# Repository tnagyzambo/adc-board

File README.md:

# e003-adc-board

Analog data acquisition board for the ASRP ECU stack. Two general-purpose
channels, sampled simultaneously, configured through an onboard FPGA for load
cells, piezoresistive pressure transducers, 4-20 mA and voltage transmitters,
and referenced to the stack's ground. The thermocouple channels are
`e004-tc-board`. Boards stack to add channels on ASRP-PCB-INTERCONNECT-2,
defined in the design summary, which brings them power from `e001-power-board`
through the ECU MCU board and carries their data to it. The ECU MCU board logs
the data. 60 x 60 mm.

The schematic is drawn; the board has not yet been laid out.

## Documentation

`doc-design/e003-design-summary.typ` records the design intent and, once there
is a board, reviews it against that intent and the device datasheets, with the
schematic as an appendix.

The report builds with [`dcs`](../../../code/dcs). It is built twice:
`e003-design-summary-a4.pdf` to print single sided and keep loose leaf, and
`e003-design-summary-b5.pdf` to print duplex and file in a binder.

```
cd doc-design
dcs build            # or `dcs watch`, or `dcs clean`
dcs open             # editor, build and viewer in one zellij session
```

Everything generated lands in `doc-design/assets/` and is ignored. The footer
stamp names the last commit that touched the report: build after committing and
it names that commit, build mid-edit and it says so.

## Gateware

`gateware/` holds the FPGA's VHDL. The current design is a bring-up image: it
answers on SPI0 with a hello-world string, measures `SYNC_CLK`, switches the
channel supply on command and reads both converters' ID registers. It is
simulated with GHDL and built with Lattice Diamond, both in one Docker
container, and programmed natively from macOS through a J-Link on the
Tag-Connect footprint; `gateware/README.md` gives the full procedure.

## Repository

Part of the ASRP ECU stack. Each board is its own repo, sitting side by
side under `ecad/projects/`: `e001-power-board`, `e002-mcu-board`,
`e003-adc-board`, `e004-tc-board`, `bus-interface`, `ecu-stack` and
`servo-board`. They are separate because they are drawn, revised, fabricated
and released one at a time. Nothing in the KiCad files crosses a board
boundary.

## Branches

- `main` — released revisions and nothing else. One commit per revision,
  squashed from `dev` at release, with the revision in the commit subject:
  `REV A`, `REV B`. `git log --oneline main` is the revision list.
- `dev` — everything in progress.

There are no tags. A revision is a commit on `main`.

This board has no revision yet, so `main` carries only its initial commit, an
empty README. Everything, this README included, lives on `dev`.

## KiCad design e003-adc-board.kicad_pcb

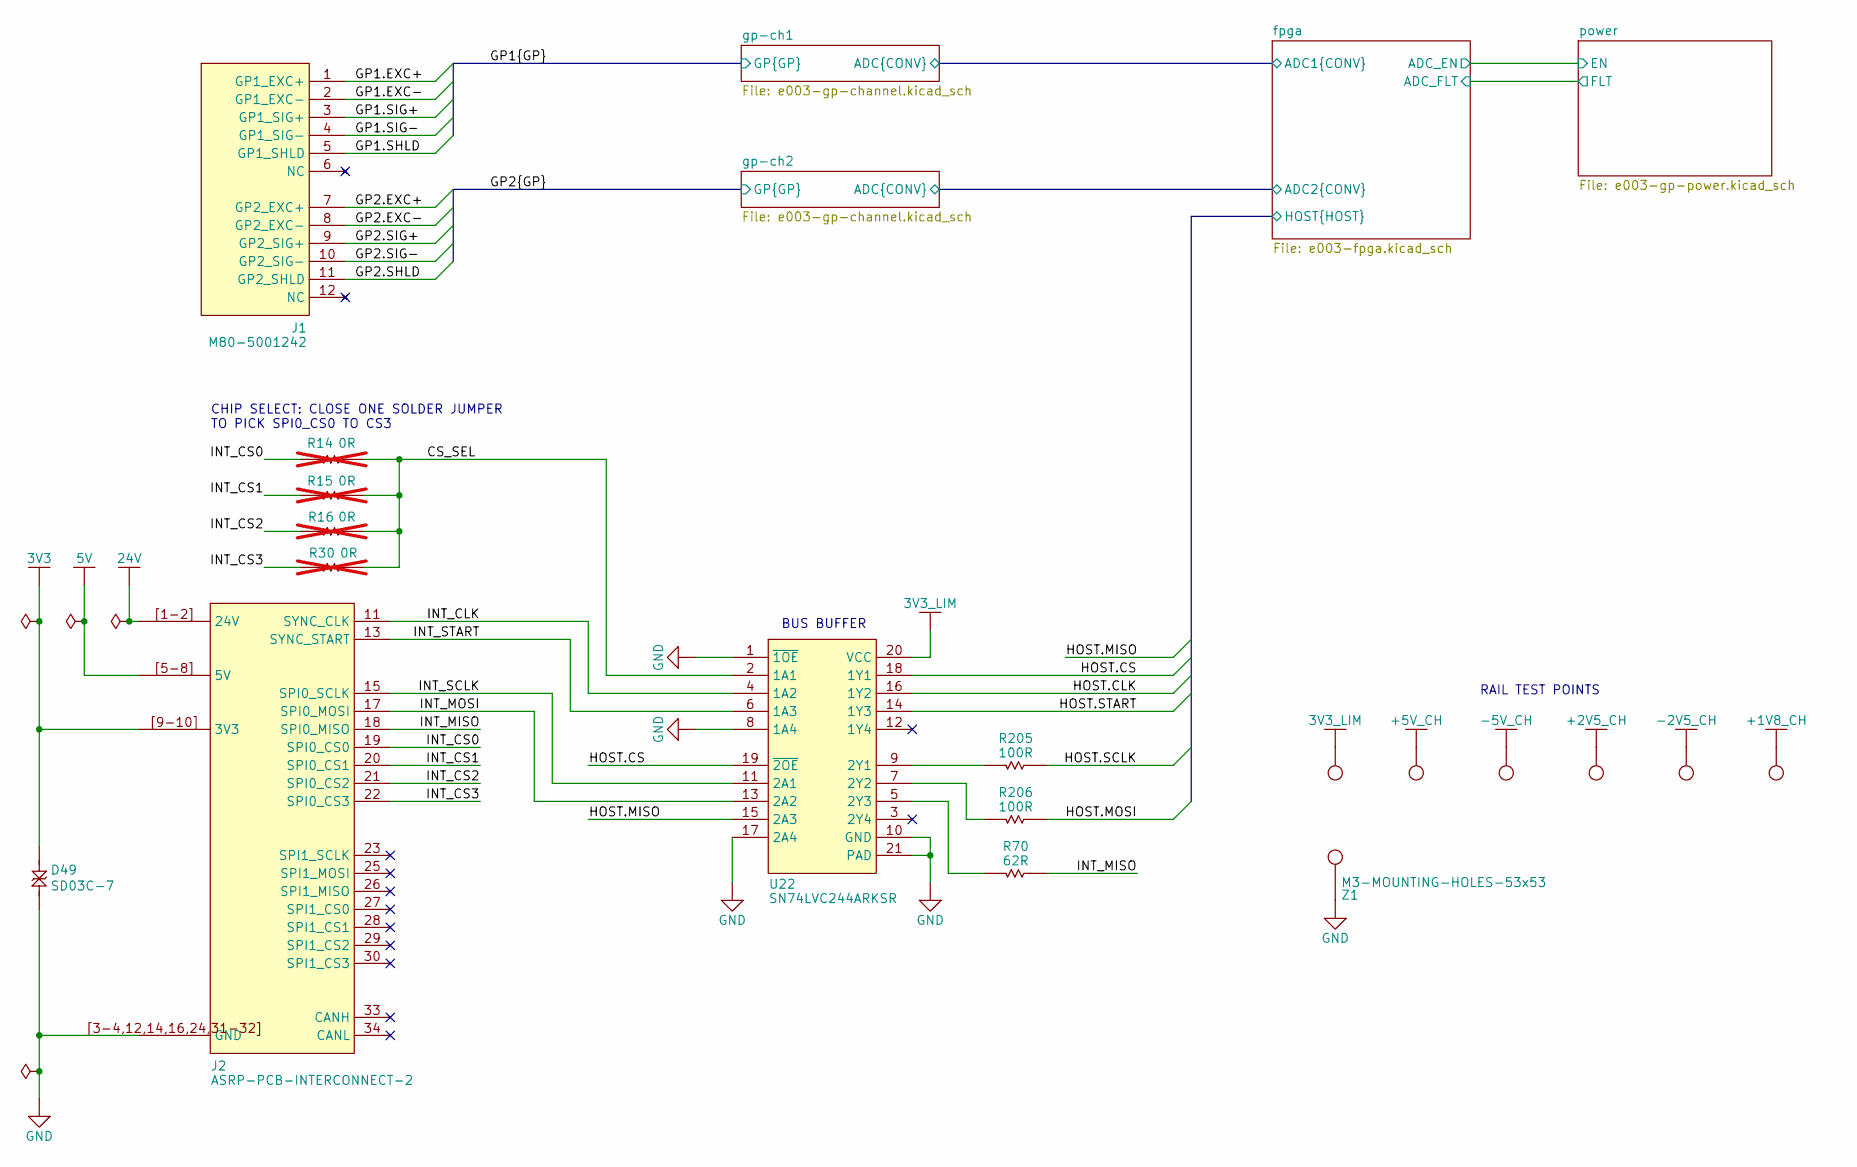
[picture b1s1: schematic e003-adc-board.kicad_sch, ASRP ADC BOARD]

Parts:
D49: SD03C-7; DIODES-SOD323; Voltage_Rating 3.3V; MPN SD03C-7; DigiKey_Part 31-SD03C-7CT-ND
J1: M80-5001242; HARWIN-M80-5001242; MPN M80-5001242; DigiKey_Part 952-1980-ND
J2: ASRP-PCB-INTERCONNECT-2
R14, R15, R16, R30: 0R; VISHAY-0402; Tolerance 1%; MPN CRCW04020000Z0EEHP; DigiKey_Part 541-CRCW04020000Z0EEHPCT-ND; not fitted
R70: 62R; VISHAY-0402; Tolerance 1%; MPN CRCW040262R0FKEDC; DigiKey_Part 541-CRCW040262R0FKEDCCT-ND
R205, R206: 100R; VISHAY-0402; Tolerance 1%; MPN CRCW0402100RFKEDC; DigiKey_Part 541-3962-1-ND
TP2, TP10, TP11, TP12, TP13, TP14: PCB-TEST-POINT; PCB-PROBEPOINT; MPN N/A
U22: SN74LVC244ARKSR; TI-VQFN-RKS0020C; MPN SN74LVC244ARKSR; DigiKey_Part 296-SN74LVC244ARKSRCT-ND
Z1: M3-MOUNTING-HOLES-53x53; PCB-M3-MOUNTING-HOLES-53x53; MPN N/A

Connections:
3V3: D49.1 (A1), J2.[9-10] (3V3); also elsewhere on the board
3V3_LIM: TP2.1 (0_1), U22.20 (VCC); also elsewhere on the board
+1V8_CH: TP14.1 (0_1); also elsewhere on the board
+2V5_CH: TP12.1 (0_1); also elsewhere on the board
+5V_CH: TP10.1 (0_1); also elsewhere on the board
-2V5_CH: TP13.1 (0_1); also elsewhere on the board
-5V_CH: TP11.1 (0_1); also elsewhere on the board
/CS_SEL: R14.1, R15.1, R16.1, R30.1, U22.2 (1A1)
/GP1.EXC+: J1.1 (GP1_EXC+); also elsewhere on the board
/GP1.EXC-: J1.2 (GP1_EXC-); also elsewhere on the board
/GP1.SHLD: J1.5 (GP1_SHLD); also elsewhere on the board
/GP1.SIG+: J1.3 (GP1_SIG+); also elsewhere on the board
/GP1.SIG-: J1.4 (GP1_SIG-); also elsewhere on the board
/GP2.EXC+: J1.7 (GP2_EXC+); also elsewhere on the board
/GP2.EXC-: J1.8 (GP2_EXC-); also elsewhere on the board
/GP2.SHLD: J1.11 (GP2_SHLD); also elsewhere on the board
/GP2.SIG+: J1.9 (GP2_SIG+); also elsewhere on the board
/GP2.SIG-: J1.10 (GP2_SIG-); also elsewhere on the board
/INT_CLK: J2.11 (SYNC_CLK), U22.4 (1A2)
/INT_CS0: J2.19 (SPI0_CS0), R14.2
/INT_CS1: J2.20 (SPI0_CS1), R15.2
/INT_CS2: J2.21 (SPI0_CS2), R16.2
/INT_CS3: J2.22 (SPI0_CS3), R30.2
/INT_MISO: J2.18 (SPI0_MISO), R70.1
/INT_MOSI: J2.17 (SPI0_MOSI), U22.13 (2A2)
/INT_SCLK: J2.15 (SPI0_SCLK), U22.11 (2A1)
/INT_START: J2.13 (SYNC_START), U22.6 (1A3)
/fpga/HOST.CLK: U22.16 (1Y2); also elsewhere on the board
/fpga/HOST.CS: U22.18 (1Y1), U22.19 (~2OE); also elsewhere on the board
/fpga/HOST.MISO: U22.15 (2A3); also elsewhere on the board
/fpga/HOST.MOSI: R206.1; also elsewhere on the board
/fpga/HOST.SCLK: R205.1; also elsewhere on the board
/fpga/HOST.START: U22.14 (1Y3); also elsewhere on the board
GND: D49.2 (A2), J2.[3-4,12,14,16,24,31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 (GND), U22.1 (~1OE), U22.8 (1A4), U22.10 (GND), U22.17 (2A4), U22.21 (PAD), Z1.1; also elsewhere on the board
unnamed: R205.2, U22.9 (2Y1)
unnamed: R206.2, U22.7 (2Y2)
unnamed: R70.2, U22.5 (2Y3)

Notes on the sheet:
CHIP SELECT: CLOSE ONE SOLDER JUMPER TO PICK SPI0_CS0 TO CS3
RAIL TEST POINTS
BUS BUFFER

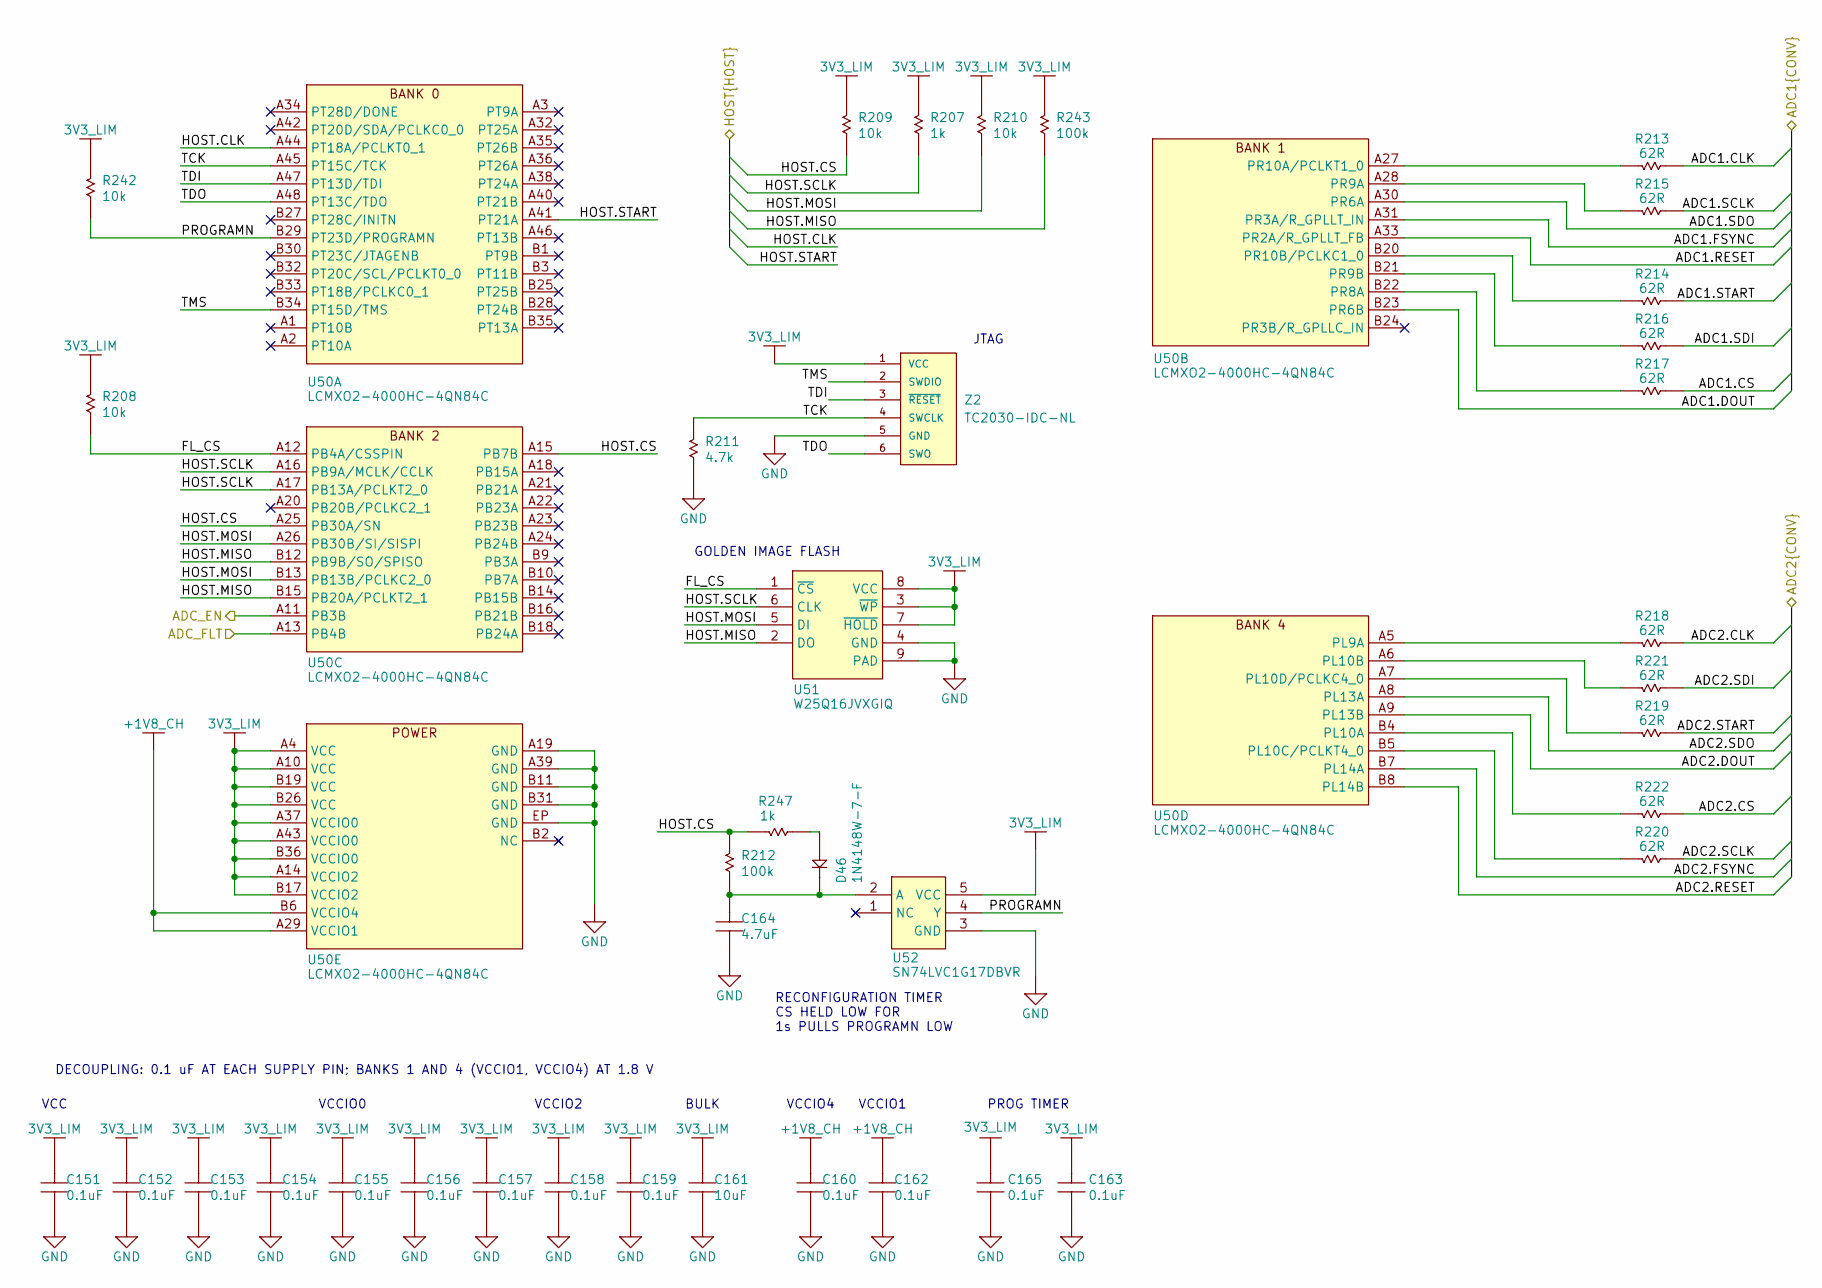
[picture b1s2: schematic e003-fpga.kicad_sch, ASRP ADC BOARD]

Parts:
C151, C152, C153, C154, C155, C156, C157, C158, C159, C160, C162, C163, C165: 0.1uF; MURATA-0402; Tolerance 10%; Voltage_Rating 50 VDC; MPN GRM155R71H104KE14J; DigiKey_Part 490-13342-2-ND
C161: 10uF; MURATA-0805; Tolerance 10%; Voltage_Rating 25 VDC; MPN GRM21BZ71E106KE15K; DigiKey_Part 490-GRM21BZ71E106KE15KCT-ND
C164: 4.7uF; MURATA-0805; Tolerance 10%; Voltage_Rating 25 VDC; MPN GRM21BZ71E475KE15L; DigiKey_Part 490-GRM21BZ71E475KE15LCT-ND
D46: 1N4148W-7-F; DIODES-SOD123; Voltage_Rating 100V; MPN 1N4148W-7-F; DigiKey_Part 1N4148W-FDICT-ND
R207, R247: 1k; VISHAY-0402; Tolerance 1%; MPN CRCW04021K00FKED; DigiKey_Part 541-1.00KLCT-ND
R208, R209, R210, R242: 10k; VISHAY-0402; Tolerance 1%; MPN CRCW040210K0FKEDC; DigiKey_Part 541-3959-1-ND
R211: 4.7k; VISHAY-0402; Tolerance 1%; MPN CRCW04024K70FKED; DigiKey_Part 541-4.70KLCT-ND
R212, R243: 100k; VISHAY-0402; Tolerance 1%; MPN CRCW0402100KFKEDC; DigiKey_Part 541-3960-1-ND
R213, R214, R215, R216, R217, R218, R219, R220, R221, R222: 62R; VISHAY-0402; Tolerance 1%; MPN CRCW040262R0FKEDC; DigiKey_Part 541-CRCW040262R0FKEDCCT-ND
U50: LCMXO2-4000HC-4QN84C; LATTICE-QFN84; MPN LCMXO2-4000HC-4QN84C; DigiKey_Part LCMXO2-4000HC-4QN84C-ND
U51: W25Q16JVXGIQ; WINBOND-XSON8-4X4; MPN W25Q16JVXGIQ; DigiKey_Part none
U52: SN74LVC1G17DBVR; TI-SOT23-DBV0005A; MPN SN74LVC1G17DBVR; DigiKey_Part none
Z2: TC2030-IDC-NL; PCB-TAG-TC2030-IDC-NL; MPN N/A

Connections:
3V3_LIM: C151.2, C152.2, C153.2, C154.2, C155.2, C156.2, C157.2, C158.2, C159.2, C161.2, C163.2, C165.2, R207.2, R208.2, R209.2, R210.2, R242.2, R243.2, U50.A4 (VCC), U50.A10 (VCC), U50.A14 (VCCIO2), U50.A37 (VCCIO0), U50.A43 (VCCIO0), U50.B17 (VCCIO2), U50.B19 (VCC), U50.B26 (VCC), U50.B36 (VCCIO0), U51.3 (~WP), U51.7 (~HOLD), U51.8 (VCC), U52.5 (VCC), Z2.1 (VCC); also elsewhere on the board
+1V8_CH: C160.2, C162.2, U50.A29 (VCCIO1), U50.B6 (VCCIO4); also elsewhere on the board
/fpga/ADC1.CLK: R213.1; also elsewhere on the board
/fpga/ADC1.CS: R217.1; also elsewhere on the board
/fpga/ADC1.DOUT: U50.B23 (PR6B); also elsewhere on the board
/fpga/ADC1.FSYNC: U50.A31 (PR3A/R_GPLLT_IN); also elsewhere on the board
/fpga/ADC1.RESET: U50.A33 (PR2A/R_GPLLT_FB); also elsewhere on the board
/fpga/ADC1.SCLK: R215.1; also elsewhere on the board
/fpga/ADC1.SDI: R216.1; also elsewhere on the board
/fpga/ADC1.SDO: U50.A30 (PR6A); also elsewhere on the board
/fpga/ADC1.START: R214.1; also elsewhere on the board
/fpga/ADC2.CLK: R218.1; also elsewhere on the board
/fpga/ADC2.CS: R222.1; also elsewhere on the board
/fpga/ADC2.DOUT: U50.A9 (PL13B); also elsewhere on the board
/fpga/ADC2.FSYNC: U50.B7 (PL14A); also elsewhere on the board
/fpga/ADC2.RESET: U50.B8 (PL14B); also elsewhere on the board
/fpga/ADC2.SCLK: R220.1; also elsewhere on the board
/fpga/ADC2.SDI: R221.1; also elsewhere on the board
/fpga/ADC2.SDO: U50.A8 (PL13A); also elsewhere on the board
/fpga/ADC2.START: R219.1; also elsewhere on the board
/fpga/ADC_EN: U50.A11 (PB3B); also elsewhere on the board
/fpga/ADC_FLT: U50.A13 (PB4B); also elsewhere on the board
/fpga/FL_CS: R208.1, U50.A12 (PB4A/CSSPIN), U51.1 (~CS)
/fpga/HOST.CLK: U50.A44 (PT18A/PCLKT0_1); also elsewhere on the board
/fpga/HOST.CS: R209.1, R212.2, R247.2, U50.A15 (PB7B), U50.A25 (PB30A/SN); also elsewhere on the board
/fpga/HOST.MISO: R243.1, U50.B12 (PB9B/SO/SPISO), U50.B15 (PB20A/PCLKT2_1), U51.2 (DO); also elsewhere on the board
/fpga/HOST.MOSI: R210.1, U50.A26 (PB30B/SI/SISPI), U50.B13 (PB13B/PCLKC2_0), U51.5 (DI); also elsewhere on the board
/fpga/HOST.SCLK: R207.1, U50.A16 (PB9A/MCLK/CCLK), U50.A17 (PB13A/PCLKT2_0), U51.6 (CLK); also elsewhere on the board
/fpga/HOST.START: U50.A41 (PT21A); also elsewhere on the board
/fpga/PROGRAMN: R242.1, U50.B29 (PT23D/PROGRAMN), U52.4 (Y)
/fpga/TCK: R211.2, U50.A45 (PT15C/TCK), Z2.4 (SWCLK)
/fpga/TDI: U50.A47 (PT13D/TDI), Z2.3 (~RESET)
/fpga/TDO: U50.A48 (PT13C/TDO), Z2.6 (SWO)
/fpga/TMS: U50.B34 (PT15D/TMS), Z2.2 (SWDIO)
GND: C151.1, C152.1, C153.1, C154.1, C155.1, C156.1, C157.1, C158.1, C159.1, C160.1, C161.1, C162.1, C163.1, C164.1, C165.1, R211.1, U50.A19 (GND), U50.A39 (GND), U50.B11 (GND), U50.B31 (GND), U50.EP (GND), U51.4 (GND), U51.9 (PAD), U52.3 (GND), Z2.5 (GND); also elsewhere on the board
unnamed: D46.1 (0), R247.1
unnamed: C164.2, D46.2 (1), R212.1, U52.2 (A)
unnamed: R217.2, U50.B22 (PR8A)
unnamed: R215.2, U50.A28 (PR9A)
unnamed: R216.2, U50.B21 (PR9B)
unnamed: R213.2, U50.A27 (PR10A/PCLKT1_0)
unnamed: R214.2, U50.B20 (PR10B/PCLKC1_0)
unnamed: R218.2, U50.A5 (PL9A)
unnamed: R222.2, U50.B4 (PL10A)
unnamed: R221.2, U50.A6 (PL10B)
unnamed: R220.2, U50.B5 (PL10C/PCLKT4_0)
unnamed: R219.2, U50.A7 (PL10D/PCLKC4_0)

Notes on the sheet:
VCCIO4
VCCIO2
PROG TIMER
GOLDEN IMAGE FLASH
VCC
VCCIO1
RECONFIGURATION TIMER CS HELD LOW FOR 1s PULLS PROGRAMN LOW
JTAG
BULK
DECOUPLING: 0.1 uF AT EACH SUPPLY PIN; BANKS 1 AND 4 (VCCIO1, VCCIO4) AT 1.8 V
VCCIO0

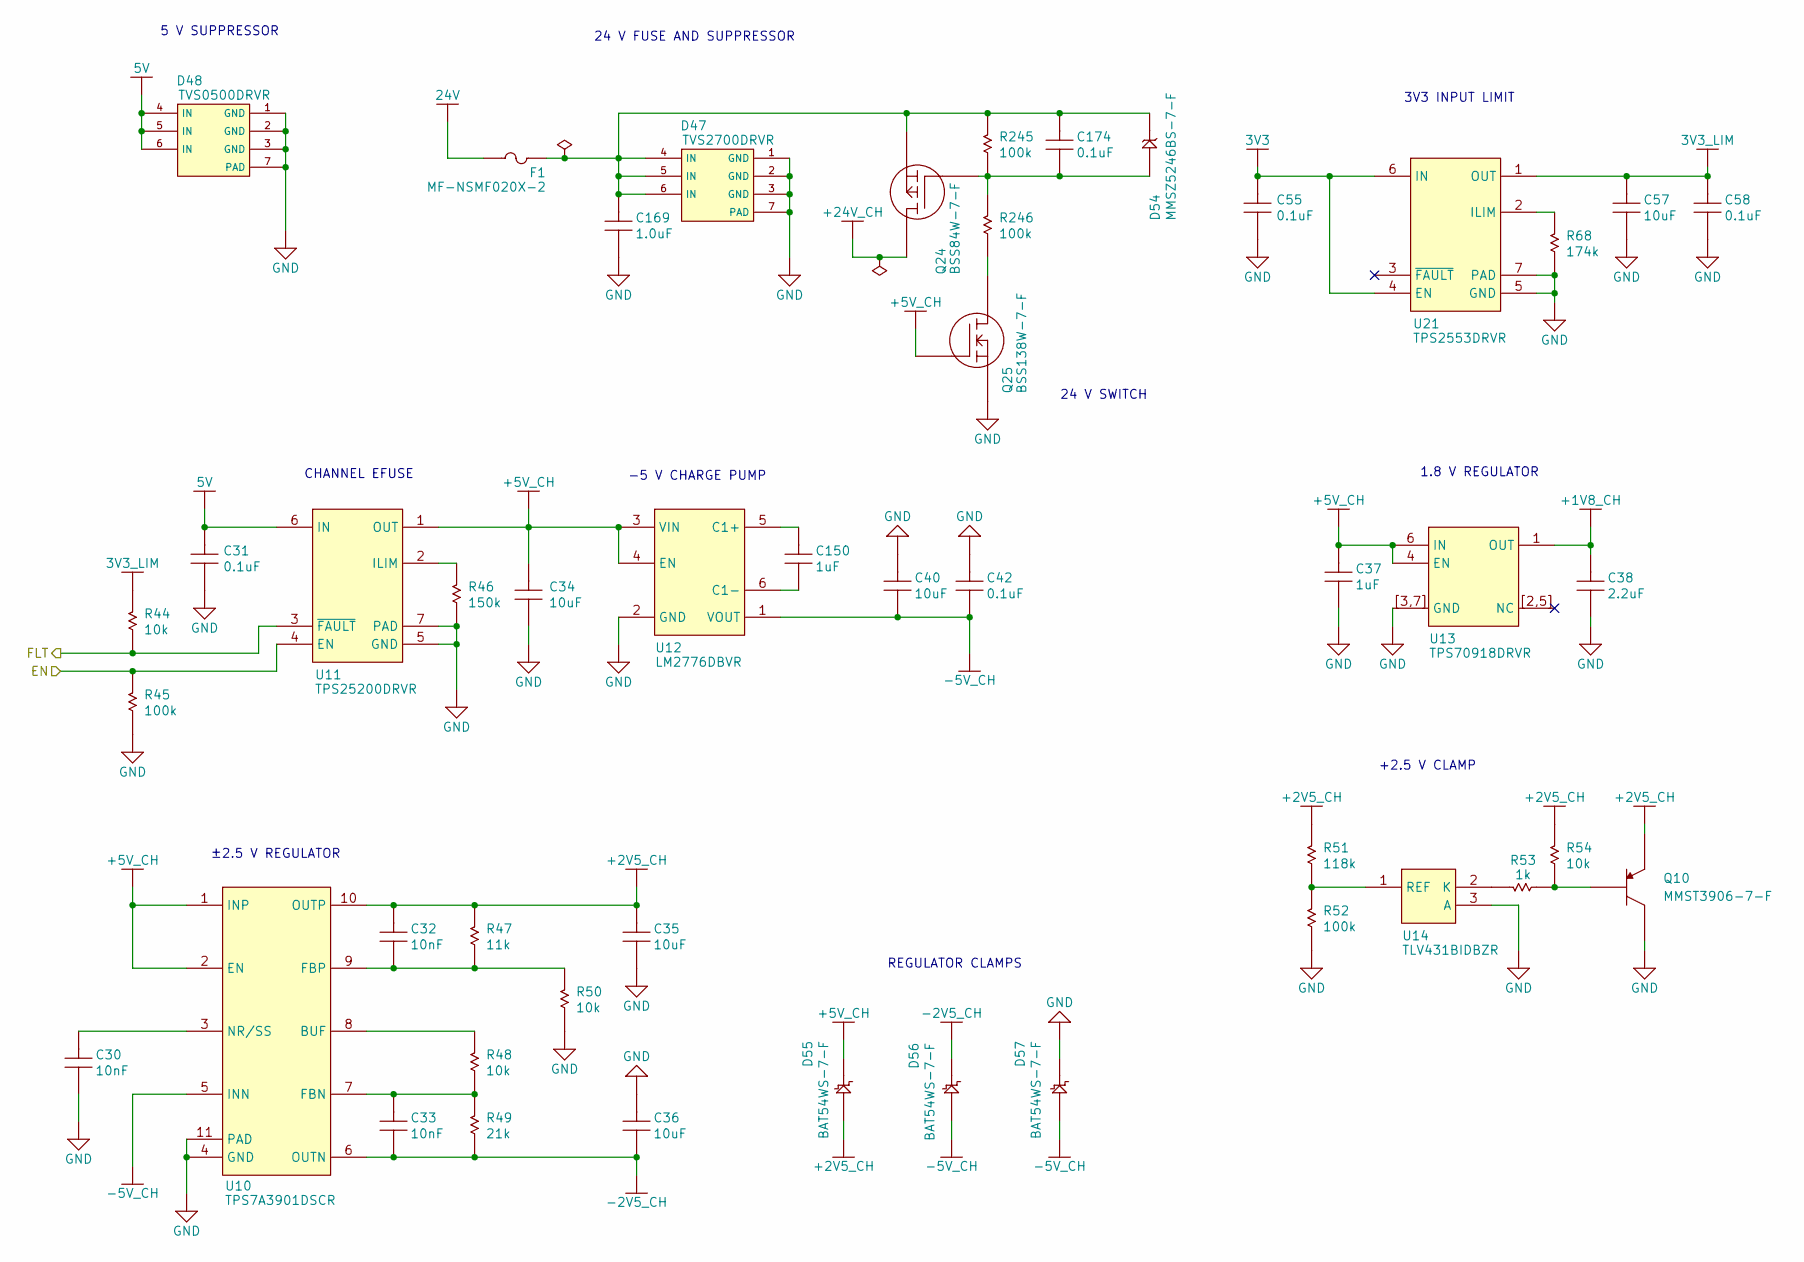
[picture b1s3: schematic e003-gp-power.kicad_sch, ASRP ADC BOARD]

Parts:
C30, C32, C33: 10nF; MURATA-0402; Tolerance 10%; Voltage_Rating 25 VDC; MPN GXT155R71E103KE01D; DigiKey_Part 490-GXT155R71E103KE01DCT-ND
C31, C42, C55, C58, C174: 0.1uF; MURATA-0402; Tolerance 10%; Voltage_Rating 50 VDC; MPN GRM155R71H104KE14J; DigiKey_Part 490-13342-2-ND
C34, C35, C36, C40, C57: 10uF; MURATA-0805; Tolerance 10%; Voltage_Rating 25 VDC; MPN GRM21BZ71E106KE15K; DigiKey_Part 490-GRM21BZ71E106KE15KCT-ND
C37, C150: 1uF; MURATA-0402; Tolerance 10%; Voltage_Rating 10 VDC; MPN GRM155Z71A105KE01D; DigiKey_Part 490-GRM155Z71A105KE01DCT-ND
C38: 2.2uF; MURATA-0402; Tolerance 10%; Voltage_Rating 10 VDC; MPN GRM155Z71A225KE01J; DigiKey_Part 490-GRM155Z71A225KE01JCT-ND
C169: 1.0uF; MURATA-0805; Tolerance 10%; Voltage_Rating 50 VDC; MPN GCJ21BR71H105KA01L; DigiKey_Part 490-10667-1-ND
D47: TVS2700DRVR; TI-WSON-DRV0006A; Voltage_Rating 27V; MPN TVS2700DRVR; DigiKey_Part 296-50512-1-ND
D48: TVS0500DRVR; TI-WSON-DRV0006A; Voltage_Rating 5V; MPN TVS0500DRVR; DigiKey_Part 296-48382-1-ND
D54: MMSZ5246BS-7-F; DIODES-SOD323; Voltage_Rating 16V; MPN MMSZ5246BS-7-F; DigiKey_Part MMSZ5246BS-FDICT-ND
D55, D56, D57: BAT54WS-7-F; DIODES-SOD323; Voltage_Rating 30V; MPN BAT54WS-7-F; DigiKey_Part BAT54WS-FDICT-ND
F1: MF-NSMF020X-2; BOURNS-MF-NSMF; Voltage_Rating 30VDC; MPN MF-NSMF020X-2; DigiKey_Part MF-NSMF020X-2CT-ND
Q10: MMST3906-7-F; DIODES-SOT323; Voltage_Rating -40V; MPN MMST3906-7-F; DigiKey_Part MMST3906-FDICT-ND
Q24: BSS84W-7-F; DIODES-SOT323; Voltage_Rating -50V; MPN BSS84W-7-F; DigiKey_Part BSS84W-FDICT-ND
Q25: BSS138W-7-F; DIODES-SOT323; Voltage_Rating 50V; MPN BSS138W-7-F; DigiKey_Part BSS138W-FDICT-ND
R44, R48, R50, R54: 10k; VISHAY-0402; Tolerance 1%; MPN CRCW040210K0FKEDC; DigiKey_Part 541-3959-1-ND
R45, R52, R245, R246: 100k; VISHAY-0402; Tolerance 1%; MPN CRCW0402100KFKEDC; DigiKey_Part 541-3960-1-ND
R46: 150k; VISHAY-0402; Tolerance 1%; MPN CRCW0402150KFKED; DigiKey_Part 541-150KLCT-ND
R47: 11k; VISHAY-0402; Tolerance 1%; MPN CRCW040211K0FKED; DigiKey_Part 541-11.0KLCT-ND
R49: 21k; VISHAY-0402; Tolerance 1%; MPN CRCW040221K0FKED; DigiKey_Part 541-21.0KLCT-ND
R51: 118k; VISHAY-0402; Tolerance 1%; MPN CRCW0402118KFKED; DigiKey_Part 541-118KLCT-ND
R53: 1k; VISHAY-0402; Tolerance 1%; MPN CRCW04021K00FKED; DigiKey_Part 541-1.00KLCT-ND
R68: 174k; VISHAY-0402; Tolerance 1%; MPN CRCW0402174KFKED; DigiKey_Part 541-174KLCT-ND
U10: TPS7A3901DSCR; TI-WSON-DSC0010J; MPN TPS7A3901DSCR; DigiKey_Part 296-TPS7A3901DSCRCT-ND
U11: TPS25200DRVR; TI-WSON-DRV0006A; MPN TPS25200DRVR; DigiKey_Part 296-37842-1-ND
U12: LM2776DBVR; TI-SOT23-DBV0006A; MPN LM2776DBVR; DigiKey_Part 296-43957-1-ND
U13: TPS70918DRVR; TI-WSON-DRV0006A; MPN TPS70918DRVR; DigiKey_Part 296-TPS70918DRVRCT-ND
U14: TLV431BIDBZR; NEXPERIA-SOT23; MPN TLV431BIDBZR; DigiKey_Part 296-17571-1-ND
U21: TPS2553DRVR; TI-WSON-DRV0006A; MPN TPS2553DRVR; DigiKey_Part 296-36006-1-ND

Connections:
3V3: C55.2, U21.4 (EN), U21.6 (IN); also elsewhere on the board
3V3_LIM: C57.2, C58.2, R44.2, U21.1 (OUT); also elsewhere on the board
5V: C31.2, D48.4 (IN), D48.5 (IN), D48.6 (IN), U11.6 (IN)
24V: F1.1
+1V8_CH: C38.2, U13.1 (OUT); also elsewhere on the board
+2V5_CH: C32.2, C35.2, D55.1 (0), Q10.2, R47.2, R51.2, R54.2, U10.10 (OUTP); also elsewhere on the board
+5V_CH: C34.2, C37.2, D55.2 (1), Q25.1, U10.1 (INP), U10.2 (EN), U11.1 (OUT), U12.3 (VIN), U12.4 (EN), U13.4 (EN), U13.6 (IN); also elsewhere on the board
+24V_CH: Q24.3; also elsewhere on the board
-2V5_CH: C33.1, C36.1, D56.2 (1), R49.1, U10.6 (OUTN); also elsewhere on the board
-5V_CH: C40.1, C42.1, D56.1 (0), D57.1 (0), U10.5 (INN), U12.1 (VOUT); also elsewhere on the board
/fpga/ADC_EN: R45.2, U11.4 (EN); also elsewhere on the board
/fpga/ADC_FLT: R44.1, U11.3 (~FAULT); also elsewhere on the board
GND: C30.1, C31.1, C34.1, C35.1, C36.2, C37.1, C38.1, C40.2, C42.2, C55.1, C57.1, C58.1, C169.1, D47.1 (GND), D47.2 (GND), D47.3 (GND), D47.7 (PAD), D48.1 (GND), D48.2 (GND), D48.3 (GND), D48.7 (PAD), D57.2 (1), Q10.3, Q25.2, R45.1, R46.1, R50.1, R52.1, R68.1, U10.4 (GND), U10.11 (PAD), U11.5 (GND), U11.7 (PAD), U12.2 (GND), U13.3 (GND), U13.7 (GND), U13.[3,7] (GND), U14.3 (A), U21.5 (GND), U21.7 (PAD); also elsewhere on the board
unnamed: C174.1, D54.1 (0), Q24.1, R245.1, R246.2
unnamed: C169.2, C174.2, D47.4 (IN), D47.5 (IN), D47.6 (IN), D54.2 (1), F1.2, Q24.2, R245.2
unnamed: Q10.1, R53.1, R54.1
unnamed: Q25.3, R246.1
unnamed: R48.2, U10.8 (BUF)
unnamed: C33.2, R48.1, R49.2, U10.7 (FBN)
unnamed: C32.1, R47.1, R50.2, U10.9 (FBP)
unnamed: C30.2, U10.3 (NR/SS)
unnamed: R46.2, U11.2 (ILIM)
unnamed: C150.2, U12.5 (C1+)
unnamed: C150.1, U12.6 (C1-)
unnamed: R53.2, U14.2 (K)
unnamed: R51.1, R52.2, U14.1 (REF)
unnamed: R68.2, U21.2 (ILIM)

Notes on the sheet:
3V3 INPUT LIMIT
±2.5 V REGULATOR
5 V SUPPRESSOR
24 V SWITCH
1.8 V REGULATOR
24 V FUSE AND SUPPRESSOR
+2.5 V CLAMP
-5 V CHARGE PUMP
REGULATOR CLAMPS
CHANNEL EFUSE

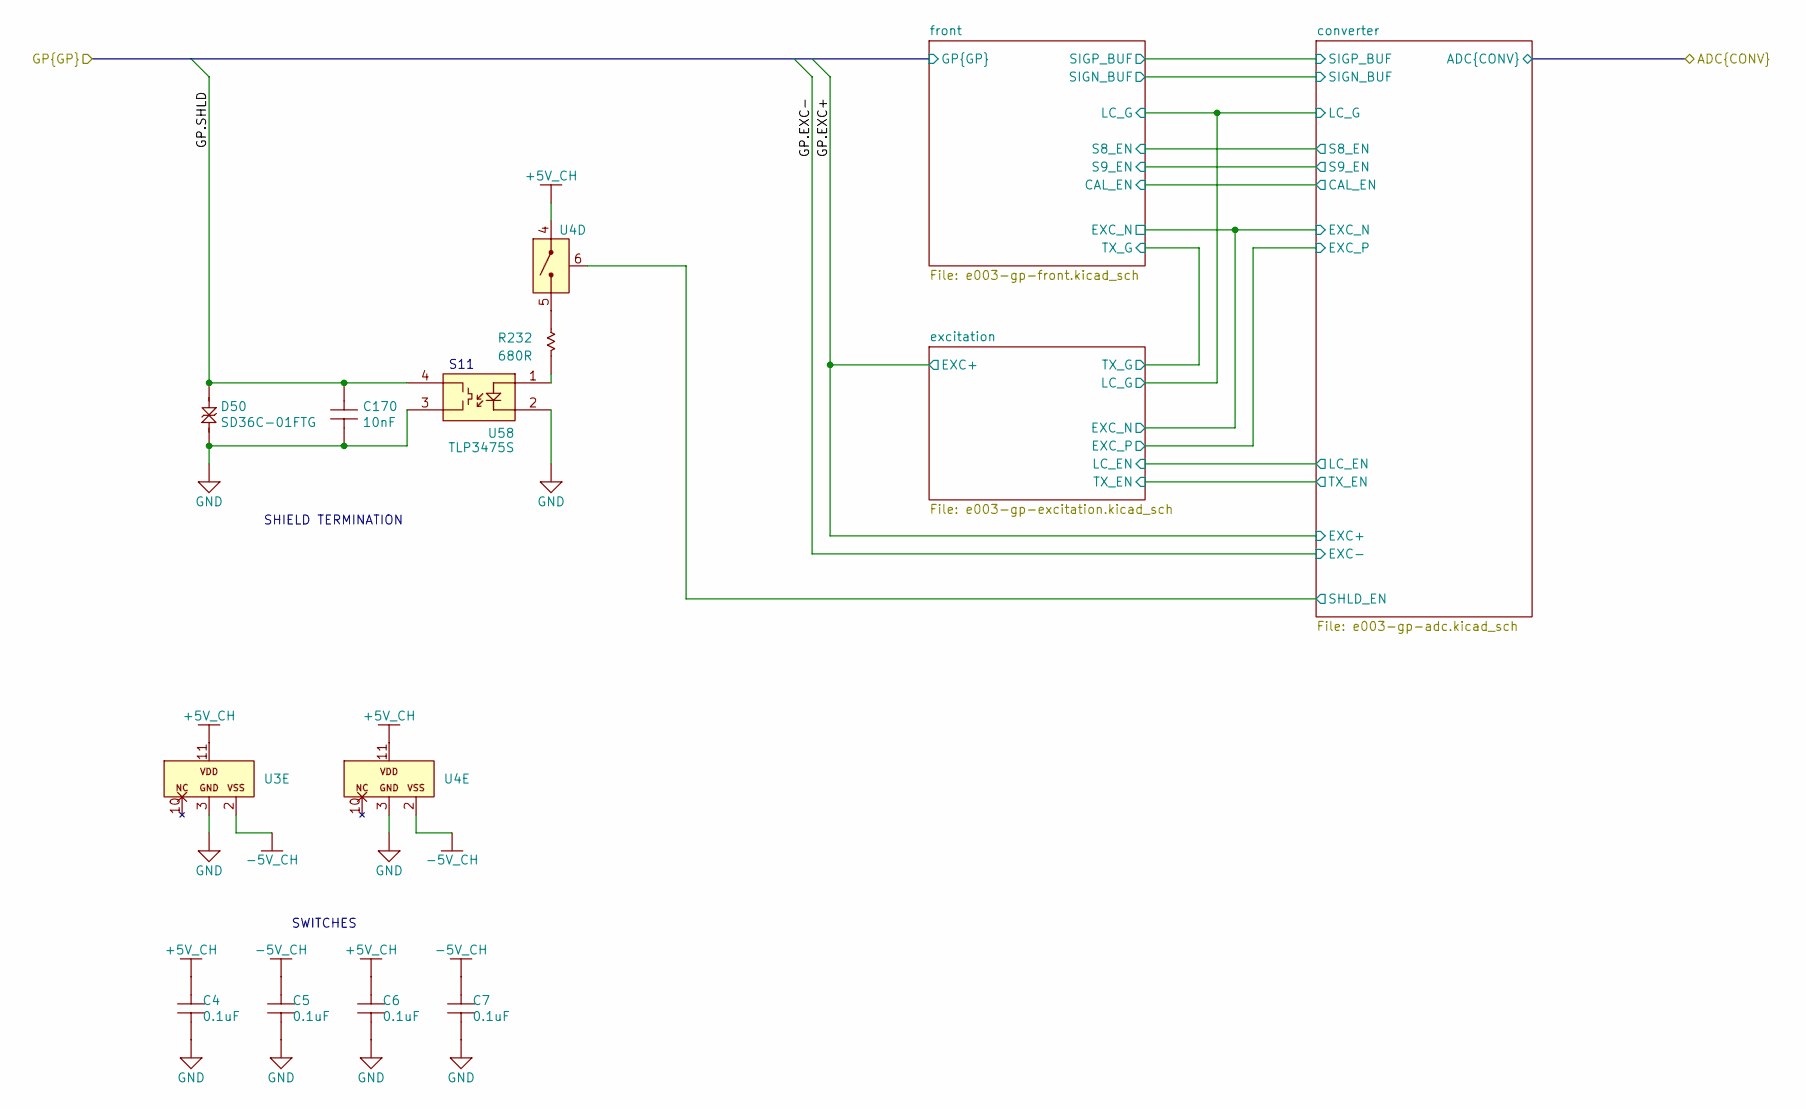
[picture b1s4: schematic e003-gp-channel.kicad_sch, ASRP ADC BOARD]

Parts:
C4, C5, C6, C7: 0.1uF; MURATA-0402; Tolerance 10%; Voltage_Rating 50 VDC; MPN GRM155R71H104KE14J; DigiKey_Part 490-13342-2-ND
C170: 10nF; MURATA-0805; Tolerance 10%; Voltage_Rating 250 VDC; MPN GRM21BR72E103KW03L; DigiKey_Part 490-3534-1-ND
D50: SD36C-01FTG; LITTELFUSE-SOD323; Voltage_Rating 36V; MPN SD36C-01FTG; DigiKey_Part F6448CT-ND
R232: 680R; VISHAY-0402; Tolerance 1%; MPN CRCW0402680RFKED; DigiKey_Part 541-680LCT-ND
U3, U4: TMUX6212RUMR; TI-WQFN-RUM0016E; MPN TMUX6212RUMR; DigiKey_Part 296-TMUX6212RUMRCT-ND
U58: TLP3475S; TOSHIBA-S-VSON4T; MPN TLP3475S; DigiKey_Part TLP3475S(TPECT-ND

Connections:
+5V_CH: C4.2, C6.2, U3.11 (VDD), U4.4 (S4), U4.11 (VDD); also elsewhere on the board
-5V_CH: C5.2, C7.2, U3.2 (VSS), U4.2 (VSS); also elsewhere on the board
/GP1.SHLD: C170.2, D50.1 (A1), U58.4 (D); also elsewhere on the board
/gp-ch1/converter/SHLD_EN: U4.6 (SEL4); also elsewhere on the board
GND: C4.1, C5.1, C6.1, C7.1, C170.1, D50.2 (A2), U3.3 (GND), U4.3 (GND), U58.2 (K), U58.3 (D); also elsewhere on the board
unnamed: R232.2, U4.5 (D4)
unnamed: R232.1, U58.1 (A)

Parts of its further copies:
C39, C41, C43, C44: 0.1uF; MURATA-0402; Tolerance 10%; Voltage_Rating 50 VDC; MPN GRM155R71H104KE14J; DigiKey_Part 490-13342-2-ND
C171: 10nF; MURATA-0805; Tolerance 10%; Voltage_Rating 250 VDC; MPN GRM21BR72E103KW03L; DigiKey_Part 490-3534-1-ND
D51: SD36C-01FTG; LITTELFUSE-SOD323; Voltage_Rating 36V; MPN SD36C-01FTG; DigiKey_Part F6448CT-ND
R233: 680R; VISHAY-0402; Tolerance 1%; MPN CRCW0402680RFKED; DigiKey_Part 541-680LCT-ND
U15, U29: TMUX6212RUMR; TI-WQFN-RUM0016E; MPN TMUX6212RUMR; DigiKey_Part 296-TMUX6212RUMRCT-ND
U59: TLP3475S; TOSHIBA-S-VSON4T; MPN TLP3475S; DigiKey_Part TLP3475S(TPECT-ND

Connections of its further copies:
+5V_CH: C39.2, C43.2, U15.1 (S1), U15.4 (S4), U15.9 (S3), U15.11 (VDD), U15.12 (S2), U29.4 (S4), U29.11 (VDD); also elsewhere on the board
-5V_CH: C41.2, C44.2, U15.2 (VSS), U29.2 (VSS); also elsewhere on the board
/GP2.EXC-: U29.1 (S1), U29.9 (S3); also elsewhere on the board
/GP2.SHLD: C171.2, D51.1 (A1), U59.4 (D); also elsewhere on the board
/gp-ch2/converter/CAL_EN: U29.7 (SEL3); also elsewhere on the board
/gp-ch2/converter/EXC_P: U29.12 (S2); also elsewhere on the board
/gp-ch2/converter/LC_EN: U29.6 (SEL4); also elsewhere on the board
/gp-ch2/converter/LC_G: U29.5 (D4); also elsewhere on the board
/gp-ch2/converter/PRT_EN: U29.15 (SEL1); also elsewhere on the board
/gp-ch2/converter/S8_EN: U15.14 (SEL2); also elsewhere on the board
/gp-ch2/converter/S9_EN: U15.7 (SEL3); also elsewhere on the board
/gp-ch2/converter/SHLD_EN: U15.6 (SEL4); also elsewhere on the board
/gp-ch2/converter/TX_EN: U15.15 (SEL1), U29.14 (SEL2); also elsewhere on the board
/gp-ch2/excitation/TX_G: U15.16 (D1); also elsewhere on the board
GND: C39.1, C41.1, C43.1, C44.1, C171.1, D51.2 (A2), U15.3 (GND), U29.3 (GND), U59.2 (K), U59.3 (D); also elsewhere on the board
unnamed 166: U15.13 (D2); also elsewhere on the board
unnamed 167: U15.8 (D3); also elsewhere on the board
unnamed: R233.2, U15.5 (D4)
unnamed 176: U29.13 (D2), U29.16 (D1); also elsewhere on the board
unnamed 177: U29.8 (D3); also elsewhere on the board
unnamed: R233.1, U59.1 (A)

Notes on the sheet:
SHIELD TERMINATION
S11
SWITCHES

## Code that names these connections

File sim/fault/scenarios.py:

"""Scenarios for the DC fault sweep: power state, channel configuration,
connected sensor and fault, each turned into ngspice lines around board.cir.

All faults and sensors are on channel 1. Channel 2 stays off with nothing
connected, and only loads the shared supplies.
"""
import os

HERE = os.path.dirname(os.path.abspath(__file__))

CONTACTS = {'EXC+': 'gp1_excp', 'EXC-': 'gp1_excn', 'SIG+': 'gp1_sigp', 'SIG-': 'gp1_sign', 'SHLD': 'gp1_shld'}

# GPIO0..GPIO6 of the converter: LC_EN, PRT_EN, TX_EN, CAL_EN, S8_EN, S9_EN,
# SHLD_EN (tab-gp-code). A bridge runs the REFP buffer; a transmitter
# leaves it off (tab-adc-config).
LINES = ('LC_EN', 'PRT_EN', 'TX_EN', 'CAL_EN', 'S8_EN', 'S9_EN', 'SHLD_EN')
CONFIGS = {
    'off': ((), 1),
    'lc': (('LC_EN',), 1),
    'lc_cal': (('LC_EN', 'CAL_EN'), 1),
    'prt': (('PRT_EN',), 1),
    'prt_cal': (('PRT_EN', 'CAL_EN'), 1),
    'i420': (('TX_EN', 'S8_EN'), 0),
    'volt': (('TX_EN', 'S9_EN'), 0),
}

# Supplies from the stack, and the FPGA's enable of the channel supply.
POWER = {
    'on': dict(v5=5.0, v24=24.0, v33=3.3, en=3.3),      # running
    'ch_off': dict(v5=5.0, v24=24.0, v33=3.3, en=0.0),  # channel supply switched off
    'stack_off': dict(v5=0.0, v24=0.0, v33=0.0, en=0.0),  # whole stack unpowered
    'no24': dict(v5=5.0, v24=0.0, v33=3.3, en=3.3),     # running, 24 V rail absent
}

# Sensors on channel 1, and the configurations each is used in.
SENSORS = {
    'none': None,
    'lc350': ('lc', 'lc_cal'),       # 350 ohm load cell
    'prt3k5': ('prt', 'prt_cal'),    # 3.5 kohm piezoresistive (Keller 7L)
    'tx420': ('i420',),              # two-wire 4-20 mA, 21 mA, with the CBL-1 link
    'txv': ('volt',),                # three-wire 0-10 V at 10 V out, 10 mA supply
}


def sensor_lines(name):
    e, x, s, n = (CONTACTS[k] for k in ('EXC+', 'EXC-', 'SIG+', 'SIG-'))
    if name == 'none':
        return []
    if name in ('lc350', 'prt3k5'):
        r = 350 if name == 'lc350' else 3500
        return ['Rbr1 %s %s %g' % (e, s, r), 'Rbr2 %s %s %g' % (s, x, r),
                'Rbr3 %s %s %g' % (e, n, r), 'Rbr4 %s %s %g' % (n, x, r)]
    if name == 'tx420':
        # Loop current from EXC+ back on SIG+, a reverse-polarity diode, and
        # the cable link from SIG- to EXC- (CBL-1).
        return ['Dtx %s tx1 DCLAMP' % e,
                'Btx tx1 %s I = {21m*pos(tanh(v(tx1,%s)/2))}' % (s, s),
                'Rlink %s %s 0.1' % (n, x)]
    if name == 'txv':
        # Supply current from EXC+ to its common on EXC-; 10 V out through
        # 100 ohm once supplied; SIG- meets the common inside the transmitter.
        return ['Dtv %s tv1 DCLAMP' % e,
                'Btv tv1 %s I = {10m*pos(tanh(v(tv1,%s)/2))}' % (x, x),
                'Btvo tvo %s V = {10*sg(v(tv1,%s)-8,0.5)}' % (x, x),
                'Rtvo tvo %s 100' % s,
                'Rtvl %s %s 0.5' % (n, x)]
    raise ValueError(name)


def fault_lines(fault):
    """('V', contact, source) sweeps a current-limited source on a contact;
    ('short', a, b)
    joins two contacts; None leaves the channel undisturbed."""
    if fault is None:
        return ['Vf fsrc 0 0', 'Rfd fsrc 0 1k']
    if fault[0] == 'V':
        _, c, src = fault
        # A source limited to src ('5A', '30mA'), 0.1 ohm below its limit.
        ilim = float(src[:-2]) * 1e-3 if src.endswith('mA') else float(src[:-1])
        return ['Vf fsrc 0 0', 'Bf fsrc %s I = {%g*tanh(v(fsrc,%s)/(%g*0.1))}' % (CONTACTS[c], ilim, CONTACTS[c], ilim)]
    if fault[0] == 'short':
        # The short closes once the channel is running: its conductance
        # rises from 20 nS to 20 S (0.05 ohm), log-linearly over T_SHORT.
        a, b = CONTACTS[fault[1]], CONTACTS[fault[2]]
        return ['Vf fsrc 0 0', 'Rfd fsrc 0 1k',
                'Bsh %s %s I = {v(%s,%s)*20*exp(-21*(1-min(max((time-%g)/%g,0),1)))}' % (a, b, a, b, T_ON, T_SHORT)]
    raise ValueError(fault)


# The sweep runs as a slow transient, because the operating point of the
# whole channel does not converge from cold: the supplies ramp up over 1 ms,
# the switch lines come up at 1.4 ms, everything has settled by T_ON, and the fault source then ramps at 1 V/ms. With 10 pF on
# every node (cshunt) the slowest internal time constant is about 10 us, so
# each output point is a DC operating point to well within 1 mV.
T_ON = 2e-3
RATE = 1e3   # V/s
T_SHORT = 10e-3


def t_end(fault, vmax):
    return T_ON + (T_SHORT if fault and fault[0] == 'short' else abs(vmax) / RATE)


# Solver settings to retry a case with, should the previous ones fail: a
# few cases stall at a corner of a clamp or gate, and any of these gets past
# it without changing the circuit.
RETRIES = (
    dict(),
    dict(options=(('reltol=1e-4', 'reltol=1e-3'), ('gmin=1e-12', 'gmin=1e-10')), tmax=2e-5),
    dict(tmax=2e-5),
    dict(options=(('cshunt=1e-11', 'cshunt=1e-10'), ('method=gear', 'method=trap'))),
)


def deck(power, config, shield, sensor, fault=None, vmax=28.0, step=1.0, attempt=0):
    """ngspice lines for one scenario: the fault source ramps from 0 to vmax
    (either sign), with output every `step` volts. attempt picks RETRIES."""
    p = POWER[power]
    on, refbuf = CONFIGS[config]
    on = set(on) | ({'SHLD_EN'} if shield else set())
    params = ['.param %s_g%d=%d' % ('ch1', i, l in on) for i, l in enumerate(LINES)]
    params += ['.param ch1_refbuf=%d' % refbuf]
    params += ['.param ch2_g%d=0' % i for i in range(len(LINES))] + ['.param ch2_refbuf=1']
    ramp = lambda v: 'PWL(0 0 1m %g)' % v
    lines = ['* e003 GP fault sweep: %s %s shield=%d %s %s' % (power, config, shield, sensor, fault),
             '.options rshunt=1e9 cshunt=1e-11 gmin=1e-12 itl1=2000 itl2=1000 itl4=200 reltol=1e-4'
             ' abstol=1e-10 vntol=1e-5 method=gear interp noacct',
             '.include %s' % os.path.join(HERE, 'parts.lib')] + params
    lines += ['.include %s' % os.path.join(HERE, 'board.cir'),
              'Vs5 s5 0 %s' % ramp(p['v5']), 'Rs5 s5 n_5v 0.01',
              'Vs24 s24 0 %s' % ramp(p['v24']), 'Rs24 s24 n_24v 0.05',
              'Vs33 s33 0 %s' % ramp(p['v33']), 'Rs33 s33 n_3v3_lim 0.1',
              'Ven sen 0 %s' % ramp(p['en']), 'Ren sen fpga_adc_en 100']
    # 10 Mohm from every contact to GND, for the suppressors' and cable's
    # leakage: without it an open contact behind a closed switch floats on
    # 10 pF and the solver stalls.
    lines += ['Rlk_%s %s 0 10Meg' % (n, n) for ch in ('gp1', 'gp2') for n in
              ('%s_excp' % ch, '%s_excn' % ch, '%s_sigp' % ch, '%s_sign' % ch, '%s_shld' % ch)]
    lines += sensor_lines(sensor) + fault_lines(fault)
    te = t_end(fault, vmax)
    lines = [l.replace('Vf fsrc 0 0', 'Vf fsrc 0 PWL(0 0 %g 0 %g %g)' % (T_ON, te, vmax)) for l in lines]
    r = RETRIES[attempt]
    for a, b in r.get('options', ()):
        lines[1] = lines[1].replace(a, b)
    lines += ['.tran %g %g 0 %g uic' % (step / RATE, te, r['tmax']) if 'tmax' in r else
              '.tran %g %g uic' % (step / RATE, te), '.end']
    return lines


def fault_volts(n_points, vmax=28.0, step=1.0):
    """The fault source's voltage at each output point of deck()."""
    t = [k * step / RATE for k in range(n_points)]
    return [0.0 if x <= T_ON else (x - T_ON) * RATE * (1 if vmax >= 0 else -1) for x in t]

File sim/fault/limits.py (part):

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        for sel in (6, 7, 14, 15):
            L.append(Limit('SEL pin %d' % sel, Vd(sel, 3), -0.5, 38, 'V', 'TMUX6212 6.1 abs max'))
    elif sub == 'ADS127L14':
        for pin, name in ((37, 'AINP3'), (38, 'AINN3'), (39, 'AINP2'), (40, 'AINN2'), (41, 'AINP1'),
                          (42, 'AINN1'), (43, 'AINP0'), (44, 'AINN0'), (47, 'REFN'), (49, 'REFP')):
            L.append(Limit('%s clamp current' % name, I('vk%d' % pin), -10e-3, 10e-3, 'A',
                           'ADS127L14 5.1 abs max, note 2'))
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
